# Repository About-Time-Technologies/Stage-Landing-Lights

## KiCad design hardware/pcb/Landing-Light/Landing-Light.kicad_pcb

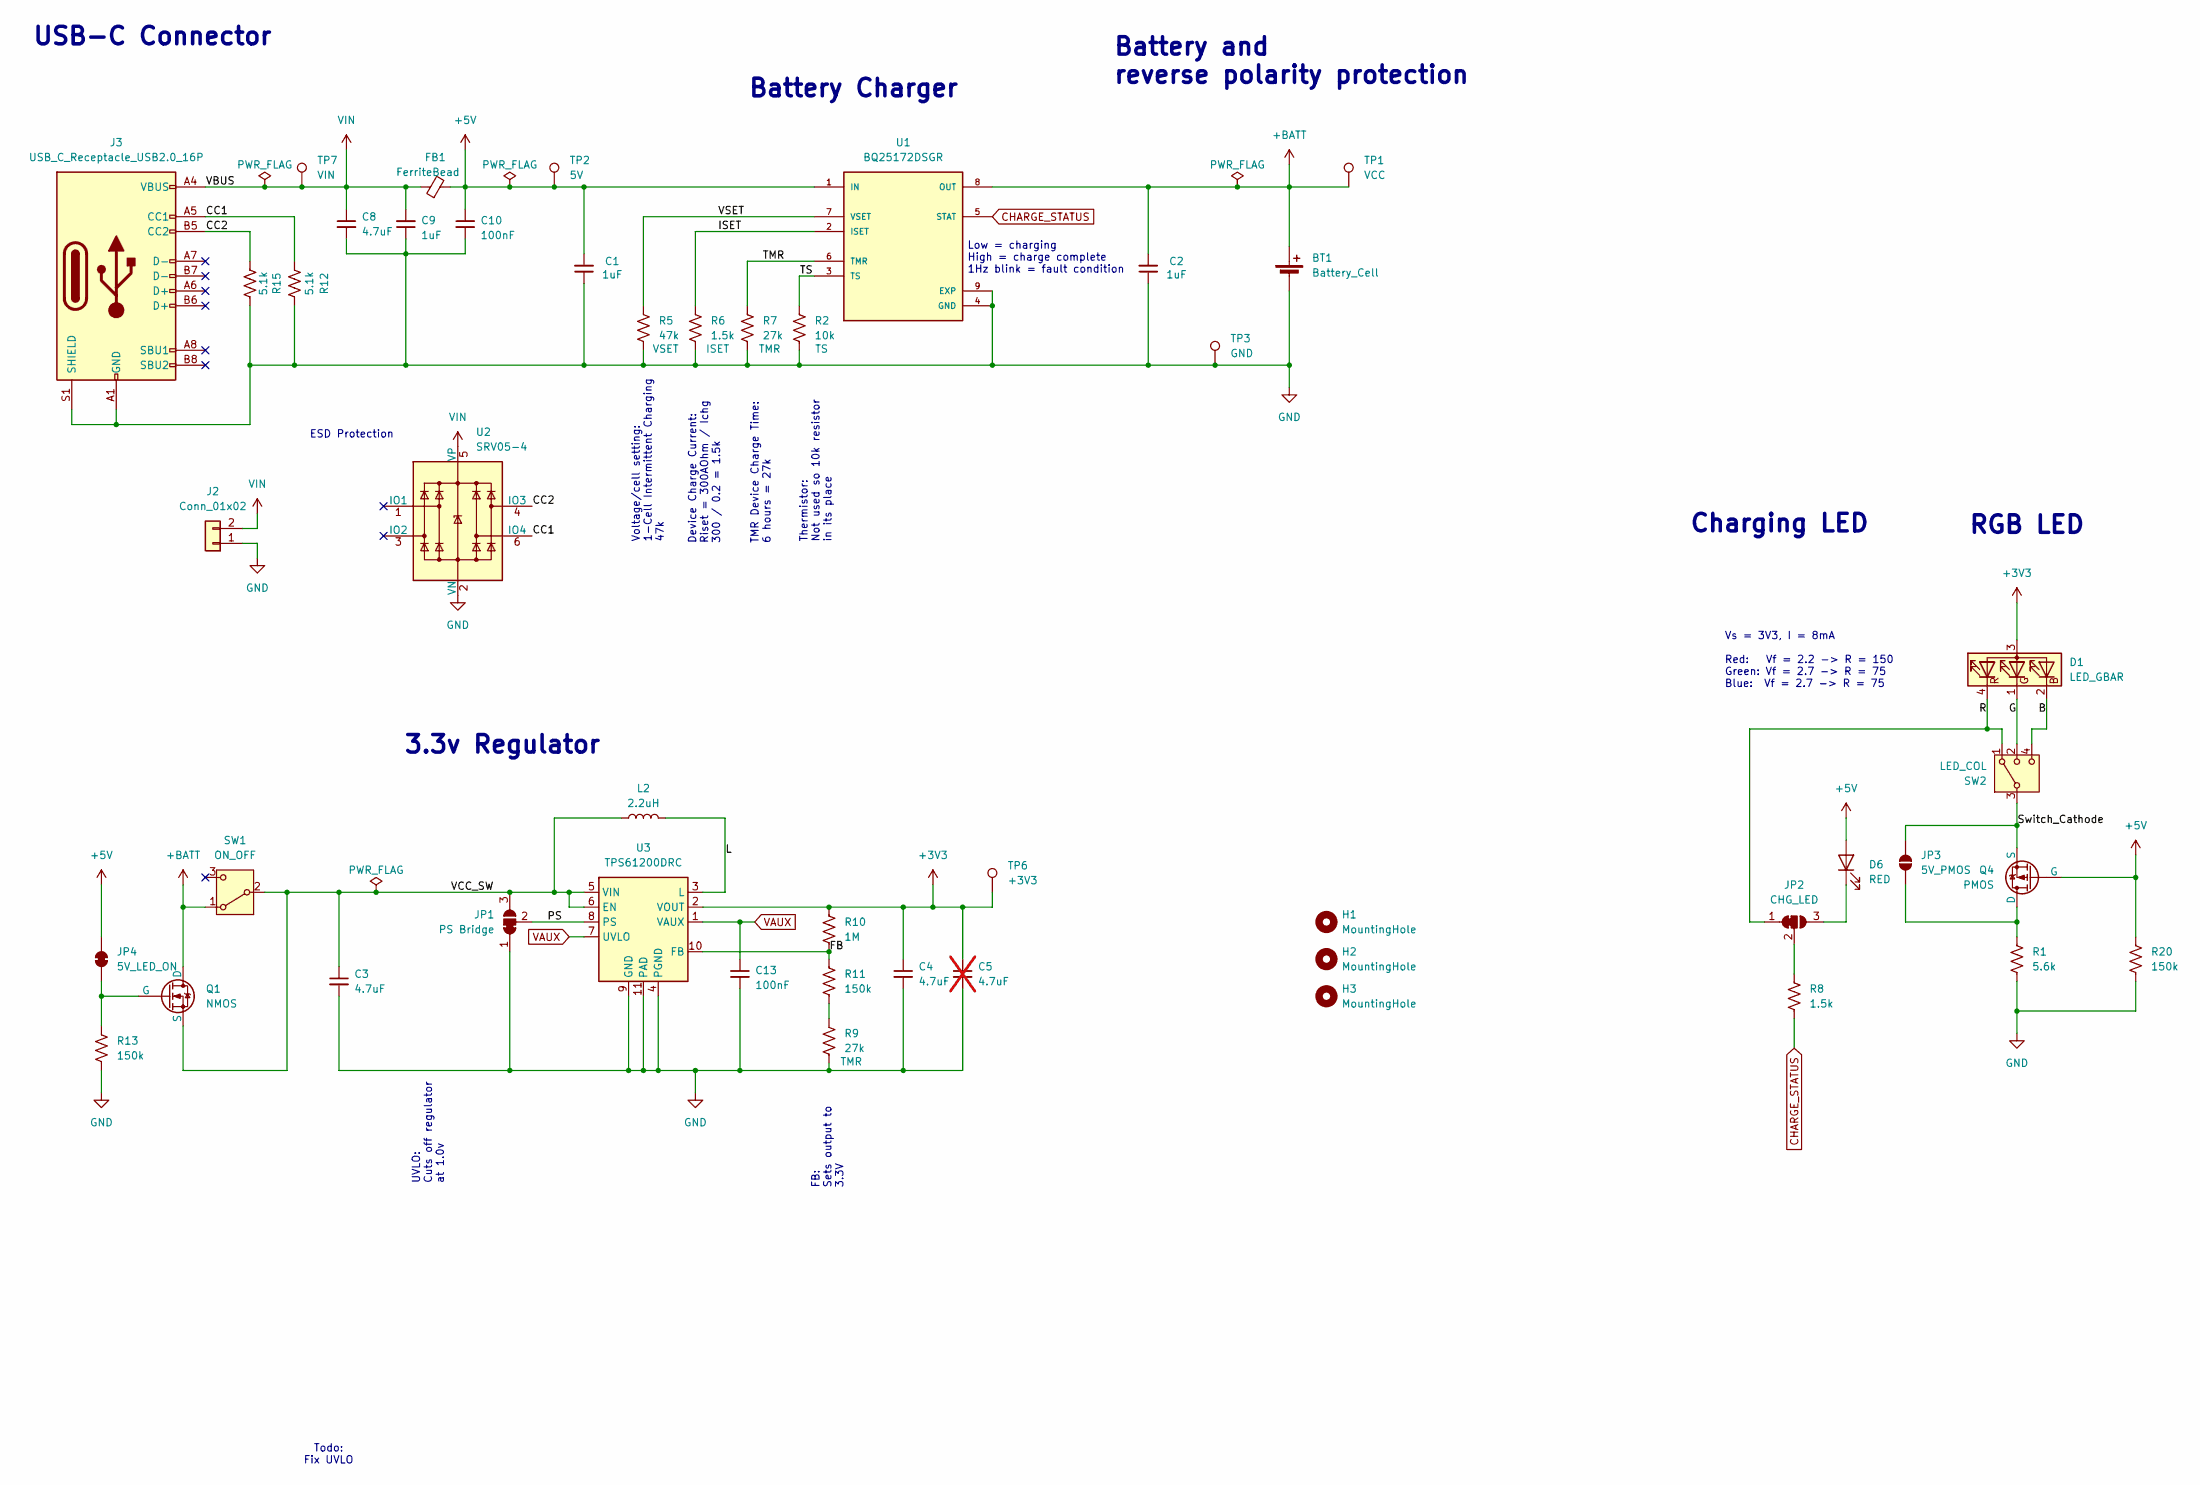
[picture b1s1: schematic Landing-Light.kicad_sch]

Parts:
BT1: Battery_Cell; AAA Side Mount
C1, C2, C9: 1uF; C_0402_1005Metric; LCSC C52923
C3, C4, C8: 4.7uF; C_0805_2012Metric; LCSC C1779
C5: 4.7uF; C_0805_2012Metric; LCSC C1779; not fitted
C10, C13: 100nF; C_0402_1005Metric; LCSC C1525
D1: LED_GBAR; LED_D5.0mm-4_RGB_Wide_Pins
D6: RED; LED_0805_2012Metric; LCSC C84256
FB1: FerriteBead; D_0805_2012Metric; LCSC C1015
H1, H2, H3: MountingHole; MountingHole_2.2mm_M2
J2: Conn_01x02; HDRRA2W46P0X254_1X2_508X279X254P
J3: USB_C_Receptacle_USB2.0_16P; USB_C_Receptacle_G-Switch_GT-USB-7010ASV; LCSC C2894897
JP1: PS Bridge; SolderJumper-3_P1.3mm_Bridged2Bar12_RoundedPad1.0x1.5mm
JP2: CHG_LED; SolderJumper-3_P1.3mm_Bridged2Bar12_RoundedPad1.0x1.5mm
JP3: 5V_PMOS; SolderJumper-2_P1.3mm_Open_RoundedPad0.5x0.75mm
JP4: 5V_LED_ON; SolderJumper-2_P1.3mm_Bridged_RoundedPad0.5x0.75mm
L2: 2.2uH; L_Sunlord_SWPA3015S; LCSC C19734
Q1: NMOS; SOT-23-3-JLCPCB; LCSC C20917
Q4: PMOS; SOT-23; LCSC C10487
R1: 5.6k; R_0402_1005Metric; LCSC C25908
R2: 10k; R_0402_1005Metric; LCSC C25744
R5: 47k; R_0402_1005Metric; LCSC C25792
R6, R8: 1.5k; R_0402_1005Metric; LCSC C25867
R7, R9: 27k; R_0402_1005Metric; LCSC C25771
R10: 1M; R_0402_1005Metric; LCSC C26083
R11, R13, R20: 150k; R_0402_1005Metric; LCSC C25755
R12, R15: 5.1k; R_0402_1005Metric; LCSC C25905
SW1: ON_OFF; SSSS810201; LCSC C231762
SW2: LED_COL; SSSS812201; LCSC C160878
TP1: VCC; TestPoint_Pad_D1.0mm
TP2: 5V; TestPoint_Pad_D1.0mm
TP3: GND; TestPoint_Pad_D1.0mm
TP6: +3V3; TestPoint_Pad_D1.0mm
TP7: VIN; TestPoint_Pad_D1.0mm
U1: BQ25172DSGR; IC_BQ25172DSGR; PARTREV June 2022; LCSC C5189434
U2: SRV05-4; SOT-363_SC-70-6; LCSC C15879
U3: TPS61200DRC; Texas_S-PVSON-N10_ThermalVias; LCSC C140320

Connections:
+3V3: C4.1, C5.1, D1.3 (A), R10.1, TP6.1 (1_1), U3.2 (VOUT)
+5V: C1.2, C10.1, D6.2 (A), FB1.2, JP4.1 (A), Q4.1 (G), R20.1, TP2.1 (1_1), U1.1 (IN)
+BATT: BT1.1 (+), C2.2, Q1.1 (D), SW1.1 (A), TP1.1 (1_1), U1.8 (OUT)
/B: D1.2 (BK), SW2.4
/CC1: J3.A5 (CC1), R12.1, U2.6 (IO4)
/CC2: J3.B5 (CC2), R15.1, U2.4 (IO3)
/FB: R10.2, R11.1, U3.10 (FB)
/G: D1.1 (GK), SW2.2
/ISET: R6.1, U1.2 (ISET)
/L: L2.2, U3.3 (L)
/PS: JP1.2 (C), U3.8 (PS)
/R: D1.4 (RK), JP2.1 (A), SW2.1
/Switch_Cathode: JP3.2 (B), Q4.2 (S), SW2.3
/TMR: R7.1, U1.6 (TMR)
/TS: R2.1, U1.3 (TS)
/VCC_SW: C3.1, JP1.3 (B), L2.1, Q1.3 (S), SW1.2 (B), U3.5 (VIN), U3.6 (EN)
/VSET: R5.1, U1.7 (VSET)
CHARGE_STATUS: R8.2, U1.5 (STAT)
GND: BT1.2 (-), C1.1, C2.1, C3.2, C4.2, C5.2, C8.2, C9.1, C10.2, C13.2, J2.1, J3.A1 (GND), J3.A12 (GND), J3.B1 (GND), J3.B12 (GND), J3.S1 (SHIELD), JP1.1 (A), R1.2, R2.2, R5.2, R6.2, R7.2, R9.2, R12.2, R13.2, R15.2, R20.2, TP3.1 (1_1), U1.4 (GND), U1.9 (EXP), U2.2 (VN), U3.4 (PGND), U3.9 (GND), U3.11 (PAD)
unnamed: D6.1 (K), JP2.3 (B)
unnamed: JP2.2 (C), R8.1
unnamed: JP3.1 (A), Q4.3 (D), R1.1
unnamed: JP4.2 (B), Q1.2 (G), R13.1
unnamed: R9.1, R11.2
VAUX: C13.1, U3.1 (VAUX), U3.7 (UVLO)
VIN: C8.1, C9.2, FB1.1, J2.2, J3.A4 (VBUS), J3.A9 (VBUS), J3.B4 (VBUS), J3.B9 (VBUS), TP7.1 (1_1), U2.5 (VP)

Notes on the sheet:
UVLO: Cuts off regulator at 1.0v
Battery and reverse polarity protection
Vs = 3V3, I = 8mA Red: Vf = 2.2 -> R = 150 Green: Vf = 2.7 -> R = 75 Blue: Vf = 2.7 -> R = 75
RGB LED
TMR Device Charge Time: 6 hours = 27k
3.3v Regulator
Battery Charger
Charging LED
Voltage/cell setting: 1-Cell Intermittent Charging 47k
Todo: Fix UVLO
FB: Sets output to 3.3V
Thermistor: Not used so 10k resistor in its place
Device Charge Current: Riset = 300AOhm / Ichg 300 / 0.2 = 1.5k
ESD Protection
Low = charging High = charge complete 1Hz blink = fault condition
USB-C Connector

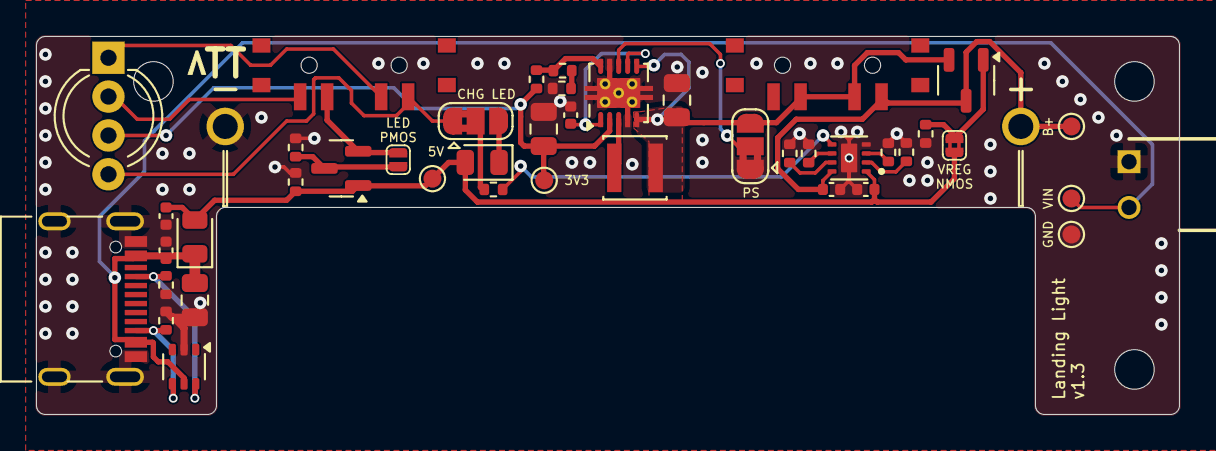
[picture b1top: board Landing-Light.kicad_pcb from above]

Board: 2 copper layers, 63.5 x 21.0 mm, 47 parts (0 on the bottom side), 26 nets.

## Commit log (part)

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2024-12-08 Basic components added
2024-12-09 Footprints complete
2024-12-09 Removing old regulator
2024-12-09 TVS Diode LCSC Number
2024-12-09 Changing to new layout
2024-12-09 Reinstating USB-C
2024-12-09 Tidying up layout
2024-12-16 Routing complete
2024-12-16 Layout labelling
2024-12-16 Adding .zip to gitignore
2024-12-16 Tidy resistor values
2024-12-18 Final layout checks
2024-12-18 Rotating silkscreen
2024-12-18 v1 Production
2024-12-18 Fix via sizes
2024-12-18 Final footprint fixes
2024-12-27 Comments added after first production run
2025-04-11 Adding new pogo connector
2025-04-13 Update power routing
2025-04-14 Complete redesign - starting point
2025-04-15 Tidying via placement
2025-04-15 Clean ground plane
2025-04-16 Finalise BOM
2025-04-16 v1.1 production
2025-11-14 Change charger connection point
2025-12-23 v1.2 notes and structure
2025-12-29 Restructuring power flow for clarity
2026-01-03 v1.2 Production
2026-01-03 Custom solder jumpers
2026-01-03 Initial files for charging board
2026-01-10 Adding notes for small fixes to v1.3
